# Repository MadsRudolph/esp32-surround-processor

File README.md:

# ESP32 surround processor

A four-speaker surround processor built around an ESP32. It takes the optical output of a TV, decodes Dolby Digital 5.1 in firmware, and drives two DACs: a front pair and a rear pair.

The receiver recovers the clocks from the optical signal and everything else follows them. The ESP32 is a slave on both of its I2S ports.

## What it does

- Dolby Digital 5.1 from the TV is decoded on the ESP32 and played on four speakers.
- Plain stereo goes to the fronts untouched, and the rears get a stereo matrix signal.
- DTS and Dolby Digital Plus are recognised and kept silent.
- A potentiometer sets the volume, and the board updates over Wi-Fi.

## The board

The board is 101.9 x 73.2 mm with copper on both faces, milled on a desktop CNC. The holes are not plated and there are no vias: the two faces meet only at 19 component leads soldered on both sides. The top face is a ground plane, and every clock, data and audio signal stays on the bottom. The layout is written as code, and a separate check proves the board is connected with bare holes, which KiCad's own rule check cannot do.

The pictures are renders made from the KiCad board file in Blender. The copper, the isolation channels, the legend and the part positions are the real design; the DAC and receiver modules are simplified stand-ins. The flat layer plots are in [docs/board.md](docs/board.md).

## Enclosure

A printed base with a laser-cut lid in 4 mm clear acrylic, held by M3 screws in heat-set inserts. The optical input, the coax input, four RCA outputs and the 9 V jack are on the rear panel, the volume knob on the front. The model uses caliper measurements of the real board and is collision-checked. The base is printed in PLA with a fuzzy-skin finish, and the box is assembled and tested (below). The files and the list of what is still assumed are in `enclosure/`.

## Measured

| | Result |
|---|---|
| Decode time | 5.3 ms average per 32 ms frame, with a film playing |
| Damaged frames | 0 in 48,044 |
| Channel separation | each channel on its own output, the others below -108 dBFS |
| Line outputs | 0.50 to 0.52 V rms at 1 kHz, -12 dBFS |
| Supply rails | 4.98 V and 3.21 V |

## Tested in the box

The finished box on its 9 V adapter, fed S/PDIF from an Analog Discovery 3 into the coax input (`tools/spdif_gen.py`), with the AD3's scope on the RCA outputs. The receiver locks in 2 to 3 s and the ESP32 reads exactly the −12.0 dBFS that is sent.

The rear matrix does what it should: half of left minus right on both rears, so a sound that is the same in both channels cancels by more than 47 dB and one that is in antiphase comes out at full level.

Every output carries its own channel at 0.46 to 0.49 V rms. That is 0.5 to 0.8 dB under the bench values, which were taken with a different signal source and different leads, so I read little into it. The right channel of each DAC is the lower one on both runs. The volume pot, mute (USER) and the mode button (BOOT) all work through the printed panel. The data and the plot script are `hardware/bench/box-test-2026-11-14.json` and `tools/plot_box_test.py`.

## What went wrong

- In the closed box on a 12 V adapter the LM317 that makes the 3.3 V got too hot, its output sagged, and the ESP32 reset from brown-out every second or so. On the 9 V adapter it is designed for, it runs without a reset. Feeding the LM317 from the 5 V rail would cut its heat by about 70 % and make a 12 V adapter safe.
- The vendor's I2S driver lost a 5 ms buffer now and then, because two interrupt handlers cleared each other's flags. A patched copy of the driver fixes it.
- The ESP32 drove its two data lines hard enough to disturb the clock lines beside them, and the DACs misread bits. The weakest drive setting is clean.
- The Dolby Digital decoder kept its FFT temporaries in doubles, and the ESP32 has no hardware for those. Single precision took the decode from 21 ms to about 5 ms per frame.

The full story is on the [project page](https://madsrudolph.dev/projects/esp32-surround-processor).

## Debug page

The board's debug page while a film plays. It shows the input format, levels and decoder health, and can play a chime or a sine sweep on one speaker at a time.

## More

- [docs/board.md](docs/board.md): file layout, rebuilding, fabrication rules, routing rules and the board concept
- [docs/firmware.md](docs/firmware.md): the firmware projects, build commands and the faults in detail
- [docs/bench.md](docs/bench.md): the bring-up page and the Analog Discovery 3
- [hardware/BUILD-NOTES.md](hardware/BUILD-NOTES.md): milling order, assembly order and module straps

## Status

The board is cut, soldered and working, and the firmware has been tested with a TV on four speakers. The enclosure is printed, assembled and tested with the AD3; the optical input with a TV in the box is next. The mute pin on the DAC modules does not mute, so mute is done in the audio data. Writing my own AC-3 decoder in place of liba52 is the next step.

## Licence

Copyright (C) 2026 Mads Rudolph. The firmware, the tools and the hardware design files
are free software under the **GNU General Public License, version 3 or (at your option)
any later version**; see `LICENSE`. They come with no warranty.

Two parts are other people's work and keep their own licences:

- `firmware/components/liba52/`: liba52 from a52dec 0.7.4, (C) Aaron Holtzman and Michel
  Lespinasse, GPL version 2 or later (`COPYING` in that folder). One file is changed, with a
  notice at its top.
- `firmware/components/esp_driver_i2s/`: the I2S driver from ESP-IDF v5.5, (C) Espressif
  Systems, Apache License 2.0 (`LICENSE` in that folder). One file is changed, with a notice
  at its top.

The firmware links both with ESP-IDF (Apache 2.0), which is why the whole is GPL version 3:
that is the GPL version compatible with the Apache licence.

"Dolby" and "Dolby Digital" are trademarks of Dolby Laboratories. This project is not made,
tested or endorsed by Dolby.

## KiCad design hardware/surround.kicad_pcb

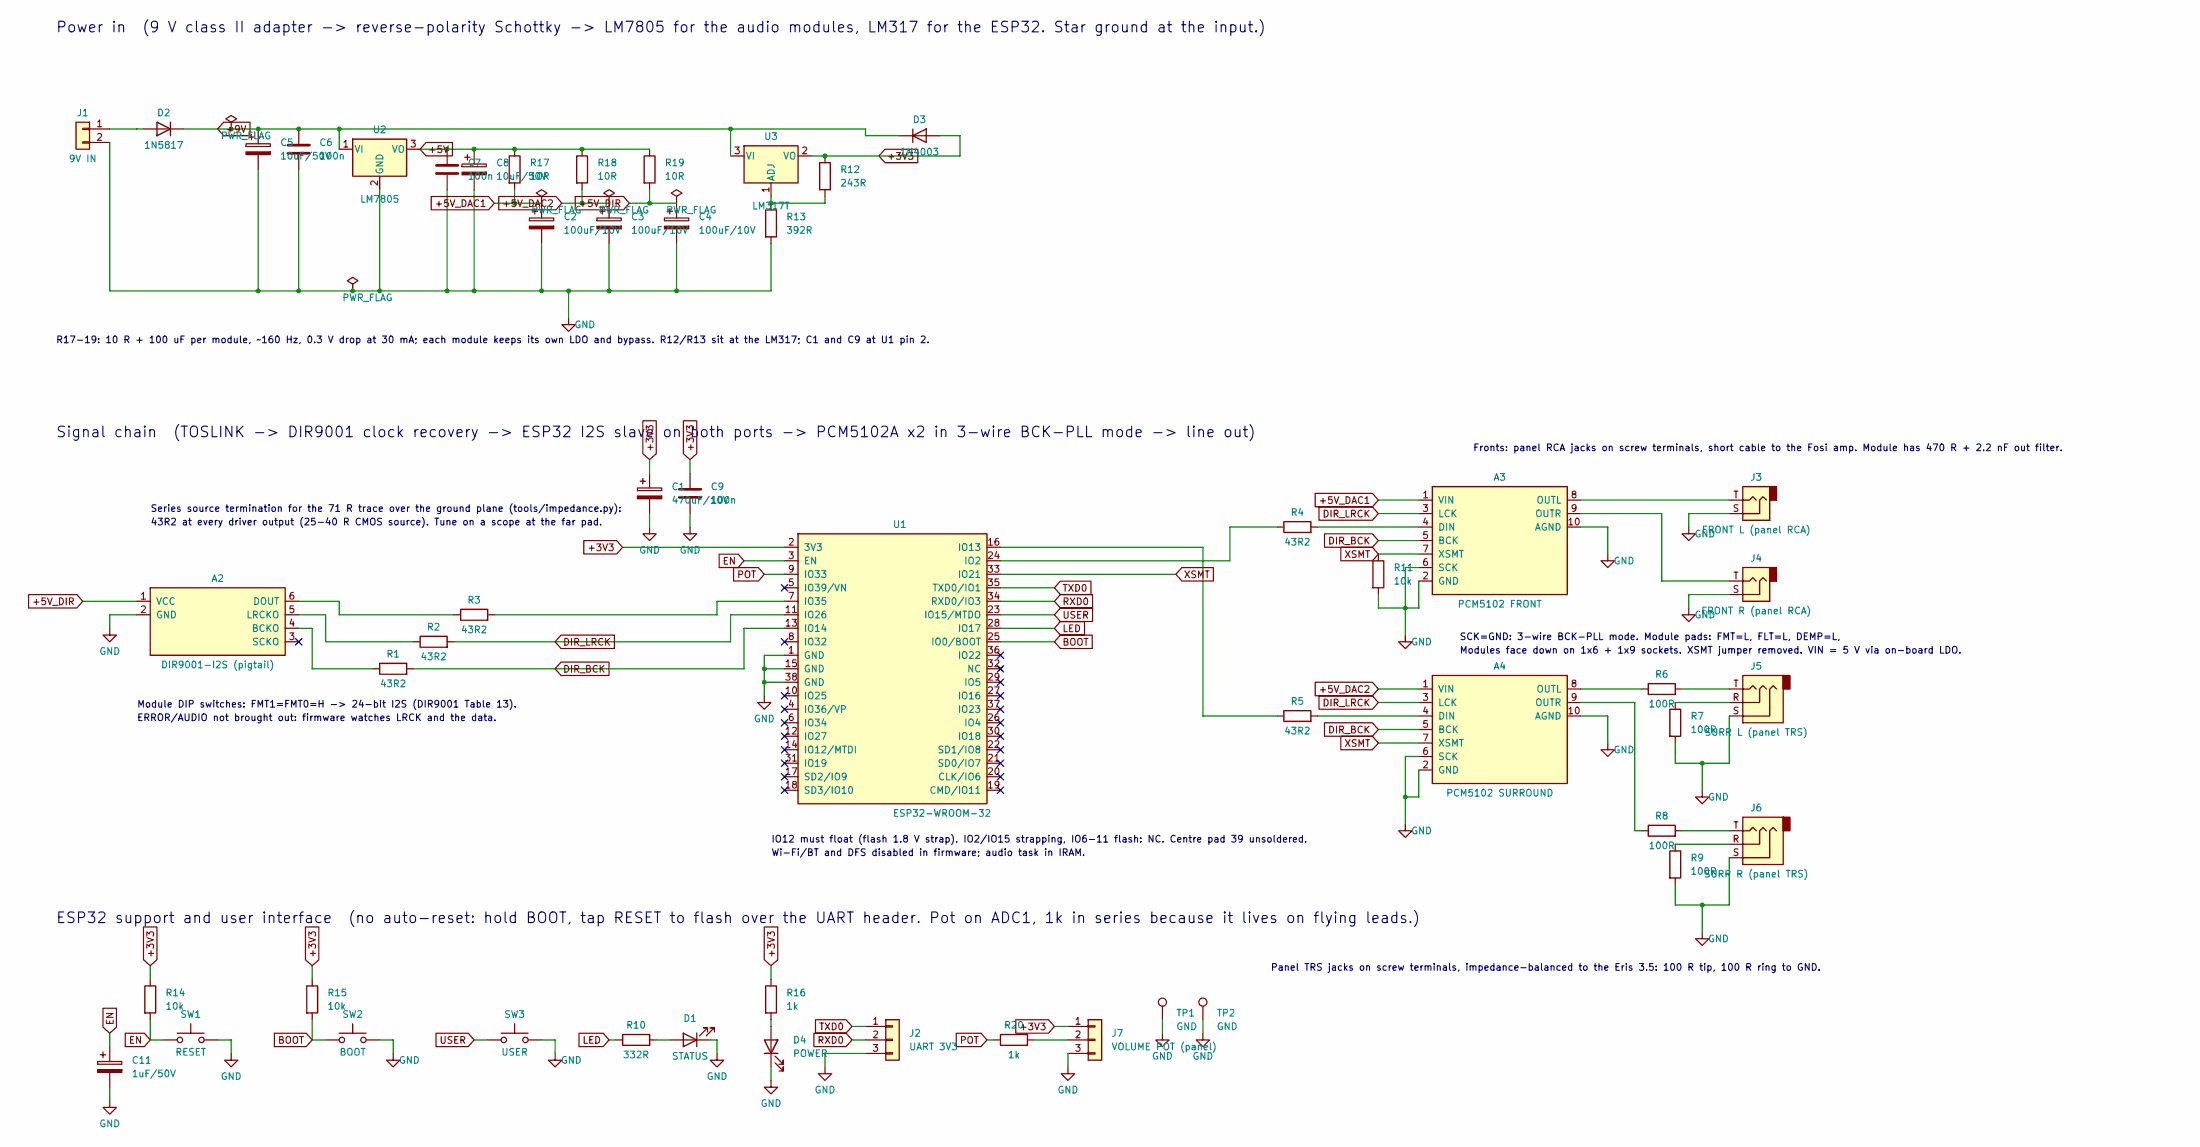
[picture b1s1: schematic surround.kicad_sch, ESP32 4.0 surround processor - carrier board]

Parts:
A2: DIR9001-I2S (pigtail); DIR9001_Pigtail_1x6
A3: PCM5102 FRONT; PCM5102_Module_FaceDown
A4: PCM5102 SURROUND; PCM5102_Module_FaceDown
C1: 470uF/10V; CP_Radial_D10.0mm_P5.00mm
C2, C3, C4: 100uF/10V; CP_Radial_D8.0mm_P5.00mm
C5, C8: 10uF/50V; CP_Radial_D5.0mm_P2.50mm
C6, C7, C9: 100n; C_Disc_D5.0mm_W2.5mm_P5.00mm
C11: 1uF/50V; CP_Radial_D5.0mm_P3.50mm_FormedLeads
D1: STATUS; LED_D3.0mm_P5.08mm_LaserPads
D2: 1N5817; D_DO-41_SOD81_P10.16mm_Horizontal
D3: 1N4003; D_DO-41_SOD81_P7.62mm_Horizontal
D4: POWER; LED_D3.0mm_P5.08mm_LaserPads
J1: 9V IN; TerminalBlock_2P_P5.08mm
J2: UART 3V3; PinHeader_1x03_P2.54mm_Vertical
J3: FRONT L (panel RCA); TerminalBlock_TS_P5.08mm
J4: FRONT R (panel RCA); TerminalBlock_TS_P5.08mm
J5: SURR L (panel TRS); TerminalBlock_TRS_P5.08mm
J6: SURR R (panel TRS); TerminalBlock_TRS_P5.08mm
J7: VOLUME POT (panel); PinHeader_1x03_P2.54mm_Vertical
R1, R2, R3, R4, R5: 43R2; R_Axial_DIN0207_L6.3mm_D2.5mm_P7.62mm_Horizontal
R6, R7, R8, R9: 100R; R_Axial_DIN0207_L6.3mm_D2.5mm_P7.62mm_Horizontal
R10: 332R; R_Axial_DIN0207_L6.3mm_D2.5mm_P7.62mm_Horizontal
R11, R14, R15: 10k; R_Axial_DIN0207_L6.3mm_D2.5mm_P7.62mm_Horizontal
R12: 243R; R_Axial_DIN0207_L6.3mm_D2.5mm_P7.62mm_Horizontal
R13: 392R; R_Axial_DIN0207_L6.3mm_D2.5mm_P7.62mm_Horizontal
R16, R20: 1k; R_Axial_DIN0207_L6.3mm_D2.5mm_P7.62mm_Horizontal
R17, R18, R19: 10R; R_Axial_DIN0207_L6.3mm_D2.5mm_P7.62mm_Horizontal
SW1: RESET; SW_PUSH_6mm
SW2: BOOT; SW_PUSH_6mm
SW3: USER; SW_PUSH_6mm
TP1, TP2: GND; TestPoint_THTPad_D2.0mm_Drill1.0mm
U1: ESP32-WROOM-32; ESP32-WROOM-32_NoVias
U2: LM7805; TO-220-3_Vertical_LaserPads
U3: LM317T; TO-220-3_Vertical_LaserPads

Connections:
+3V3: C1.1, C9.1, D3.2 (A), J7.1, R12.1, R14.1, R15.1, R16.1, U1.2 (3V3), U3.2 (VO)
+5V: C7.1, C8.1, R17.1, R18.1, R19.1, U2.3 (VO)
BOOT: R15.2, SW2.1, U1.25 (IO0/BOOT)
DIR_BCK: A3.5 (BCK), A4.5 (BCK), R1.2, U1.13 (IO14)
DIR_LRCK: A3.3 (LCK), A4.3 (LCK), R2.2, U1.11 (IO26)
EN: C11.1, R14.2, SW1.1, U1.3 (EN)
LED: R10.1, U1.28 (IO17)
unnamed: A2.4 (BCKO), R1.1
unnamed: A2.6 (DOUT), R3.1
unnamed: A2.5 (LRCKO), R2.1
unnamed: A3.4 (DIN), R4.2
unnamed: A3.8 (OUTL), J3.T
unnamed: A3.9 (OUTR), J4.T
unnamed: A4.4 (DIN), R5.2
unnamed: A4.8 (OUTL), R6.1
unnamed: A4.9 (OUTR), R8.1
unnamed: D1.2 (A), R10.2
unnamed: D2.2 (A), J1.1
unnamed: D4.2 (A), R16.2
unnamed: J5.R, R7.1
unnamed: J5.T, R6.2
unnamed: J6.R, R9.1
unnamed: J6.T, R8.2
unnamed: J7.2, R20.2
unnamed: R4.1, U1.24 (IO2)
unnamed: R5.1, U1.16 (IO13)
unnamed: R3.2, U1.7 (IO35)
unnamed: R12.2, R13.1, U3.1 (ADJ)
POT: R20.1, U1.9 (IO33)
RXD0: J2.2, U1.34 (RXD0/IO3)
TXD0: J2.1, U1.35 (TXD0/IO1)
USER: SW3.1, U1.23 (IO15/MTDO)
XSMT: A3.7 (XSMT), A4.7 (XSMT), R11.1, U1.33 (IO21)

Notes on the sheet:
Power in (9 V class II adapter -> reverse-polarity Schottky -> LM7805 for the audio modules, LM317 for the ESP32. Star ground at the input.)
R17-19: 10 R + 100 uF per module, ~160 Hz, 0.3 V drop at 30 mA; each module keeps its own LDO and bypass. R12/R13 sit at the LM317; C1 and C9 at U1 pin 2.
Signal chain (TOSLINK -> DIR9001 clock recovery -> ESP32 I2S slave on both ports -> PCM5102A x2 in 3-wire BCK-PLL mode -> line out)
Series source termination for the 71 R trace over the ground plane (tools/impedance.py):
43R2 at every driver output (25-40 R CMOS source). Tune on a scope at the far pad.
Module DIP switches: FMT1=FMT0=H -> 24-bit I2S (DIR9001 Table 13).
ERROR/AUDIO not brought out: firmware watches LRCK and the data.
IO12 must float (flash 1.8 V strap). IO2/IO15 strapping, IO6-11 flash: NC. Centre pad 39 unsoldered.
Wi-Fi/BT and DFS disabled in firmware; audio task in IRAM.
SCK=GND: 3-wire BCK-PLL mode. Module pads: FMT=L, FLT=L, DEMP=L,
Modules face down on 1x6 + 1x9 sockets. XSMT jumper removed. VIN = 5 V via on-board LDO.
Fronts: panel RCA jacks on screw terminals, short cable to the Fosi amp. Module has 470 R + 2.2 nF out filter.
Panel TRS jacks on screw terminals, impedance-balanced to the Eris 3.5: 100 R tip, 100 R ring to GND.
ESP32 support and user interface (no auto-reset: hold BOOT, tap RESET to flash over the UART header. Pot on ADC1, 1k in series because it lives on flying leads.)

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
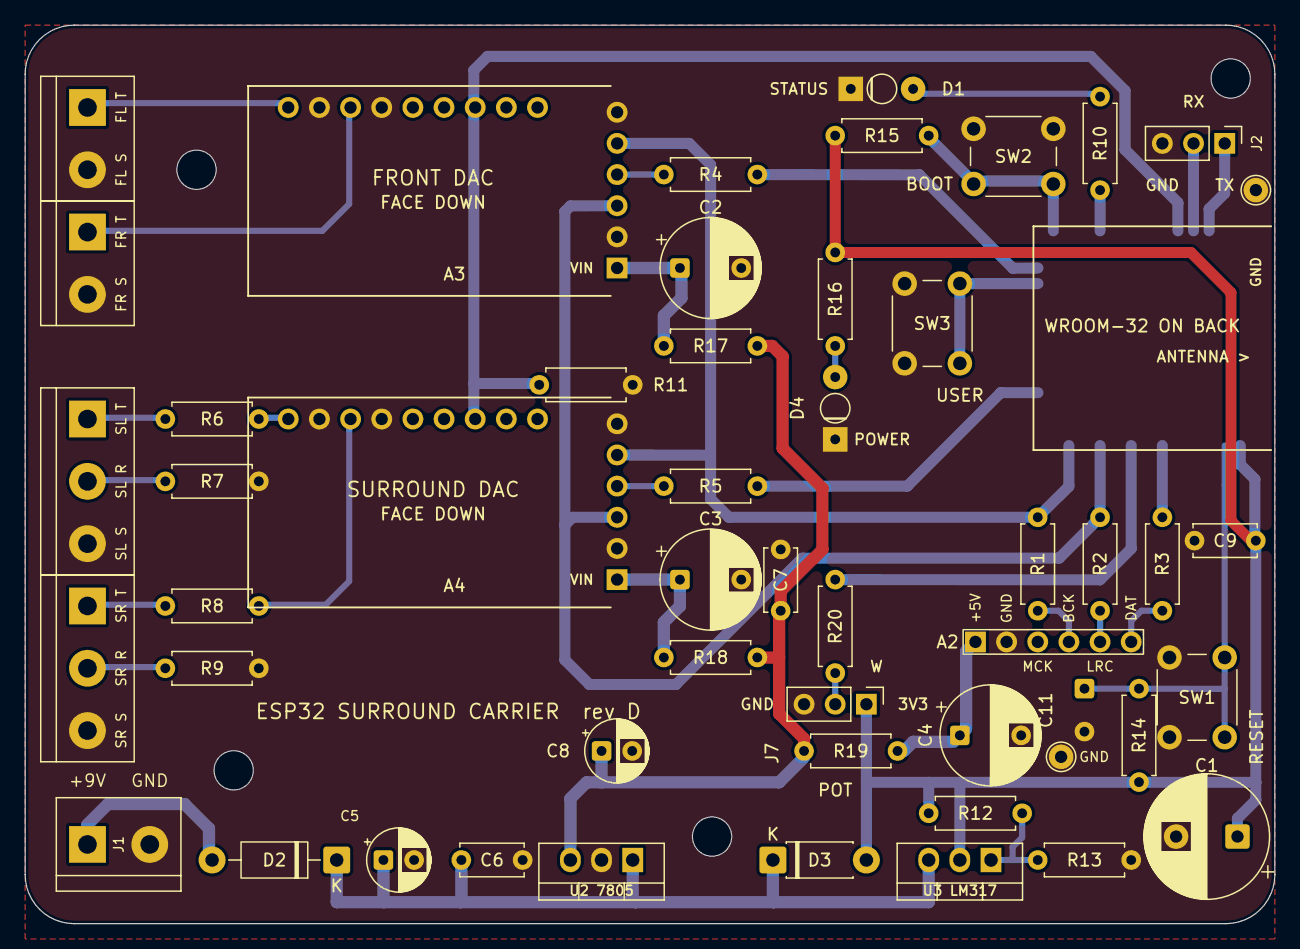
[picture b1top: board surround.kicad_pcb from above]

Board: 2 copper layers, 101.9 x 73.2 mm, 56 parts (1 on the bottom side), 38 nets.

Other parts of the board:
H1, H2, H3, H4: M3; MountingHole_3.2mm_M3

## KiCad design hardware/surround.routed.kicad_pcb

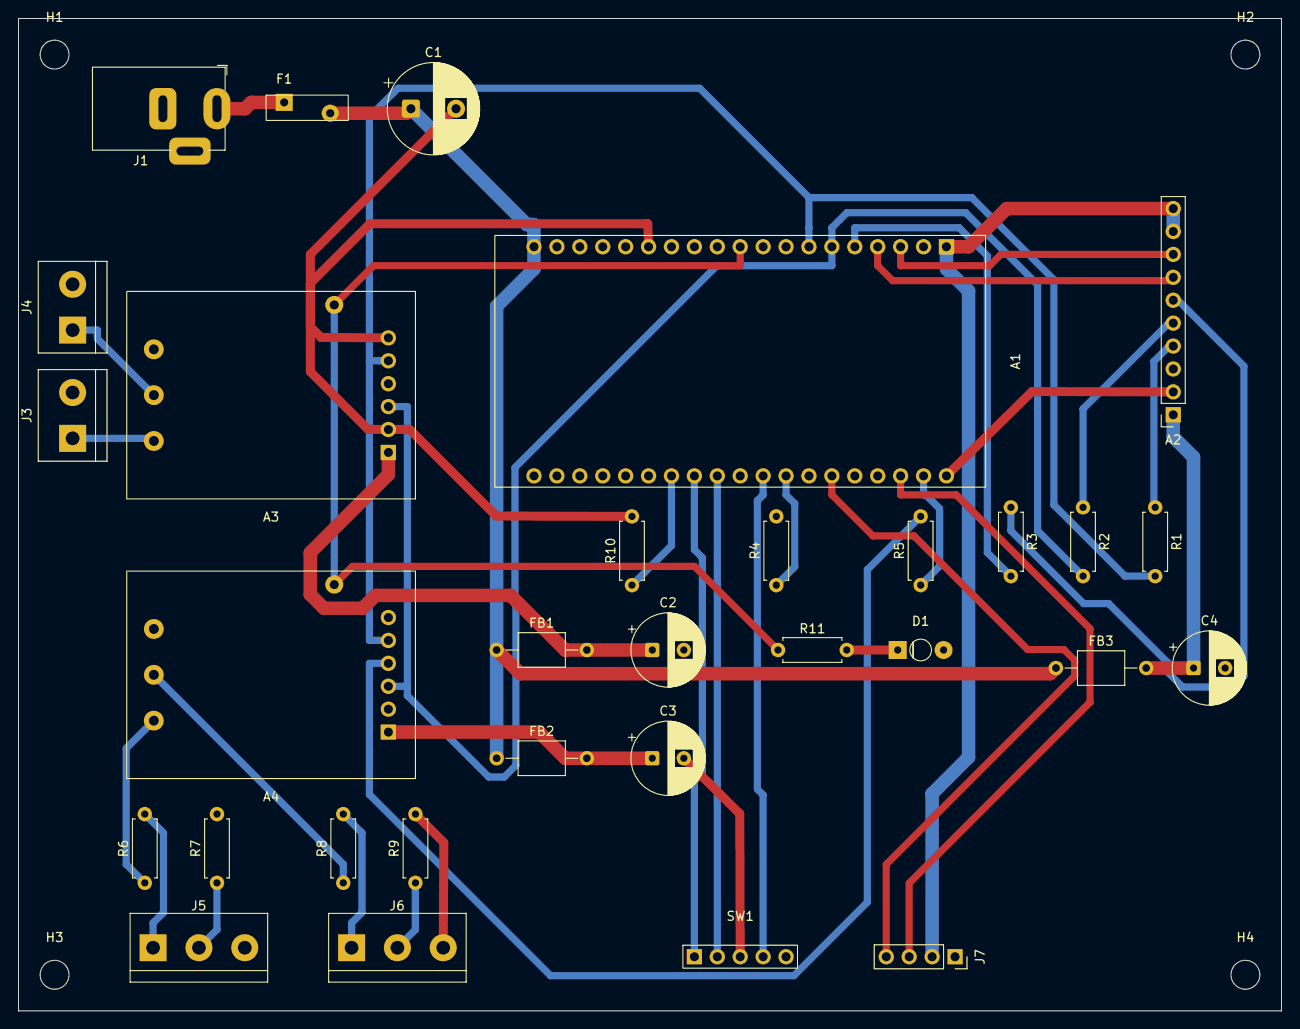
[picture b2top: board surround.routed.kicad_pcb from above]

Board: 2 copper layers, 140.0 x 110.0 mm, 35 parts (0 on the bottom side), 34 nets.

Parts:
A1: ESP32-DevKitC V4; ESP32-DevKitC-38_Sockets
A2: DIR9001 + TOSLINK; PinSocket_1x10_P2.54mm_Vertical
A3: GY-PCM5102 FRONT; GY-PCM5102_Carrier
A4: GY-PCM5102 SURROUND; GY-PCM5102_Carrier
C1: 470uF/10V; CP_Radial_D10.0mm_P5.00mm
C2, C3, C4: 100uF/10V; CP_Radial_D8.0mm_P3.50mm
D1: STATUS; LED_D3.0mm_P5.08mm_LaserPads
F1: MF-R110; Fuse_Bourns_MF-R110_P5.1mm
FB1, FB2, FB3: FB axial 600R; L_Axial_L5.0mm_D3.6mm_P10.00mm_Horizontal_Murata_BL01RN1A2A2
H1, H2, H3, H4: M3; MountingHole_3.2mm_M3
J1: PWR IN 5V; BarrelJack_Horizontal_MilledPads
J3: FRONT L (panel RCA); TerminalBlock_TS_P5.08mm
J4: FRONT R (panel RCA); TerminalBlock_TS_P5.08mm
J5: SURR L (panel TRS); TerminalBlock_TRS_P5.08mm
J6: SURR R (panel TRS); TerminalBlock_TRS_P5.08mm
J7: OLED SSD1306 I2C; PinSocket_1x04_P2.54mm_Vertical
R1, R2, R3, R4, R5: 56R; R_Axial_DIN0207_L6.3mm_D2.5mm_P7.62mm_Horizontal
R6, R7, R8, R9: 100R; R_Axial_DIN0207_L6.3mm_D2.5mm_P7.62mm_Horizontal
R10: 330R; R_Axial_DIN0207_L6.3mm_D2.5mm_P7.62mm_Horizontal
R11: 10k; R_Axial_DIN0207_L6.3mm_D2.5mm_P7.62mm_Horizontal
SW1: ENC (panel, 5 wires); PinHeader_1x05_Encoder

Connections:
+3V3: A1.1, A2.9, A2.10, J7.2
+5V: A1.19, C1.1, F1.2, FB1.1, FB2.1, FB3.1
+5V_DAC1: A3.1, C2.1, FB1.2
+5V_DAC2: A4.1, C3.1, FB2.2
+5V_DIR: A2.1, C4.1, FB3.2
DIR_BCK: A1.7, A3.5, A4.5, R1.2
DIR_LRCK: A1.6, A3.3, A4.3, R2.2
GND: A1.14, A1.20, A1.26, A2.2, A3.2, A3.6, A3.10, A4.2, A4.6, A4.10, C1.2, C2.2, C3.2, C4.2, D1.1, D1.2, J1.2, J3.S, J4.S, J5.S, J6.S, J7.1, R7.2, R9.2, R10.2, R11.2, SW1.C, SW1.S2
unnamed: A1.32, R10.1
unnamed: A1.31, SW1.A
unnamed: A1.30, SW1.B
unnamed: A1.28, SW1.S1
unnamed: A1.27, R4.1
unnamed: A1.21, R5.1
unnamed: A1.5, R3.2
unnamed: A1.3, A2.8
unnamed: A1.4, A2.7
unnamed: A2.4, R1.1
unnamed: A2.6, R3.1
unnamed: A2.5, R2.1
unnamed: A3.4, R4.2
unnamed: A3.8, J3.T
unnamed: A3.9, J4.T
unnamed: A4.4, R5.2
unnamed: A4.8, R6.1
unnamed: A4.9, R8.1
unnamed: F1.1, J1.1
unnamed: J5.R, R7.1
unnamed: J5.T, R6.2
unnamed: J6.R, R9.1
unnamed: J6.T, R8.2
SCL: A1.22, J7.3
SDA: A1.25, J7.4
XSMT: A1.10, A3.7, A4.7, R11.1

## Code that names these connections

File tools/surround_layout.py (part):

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    sh.seg(g, (G(121), g.y))
sh.seg((G(121), g1.y), (G(121), g38.y)); sh.gnd((G(121), g38.y))
ad = esp.pin("IO33")
sh.seg(ad, (G(121), ad.y)); sh.label((G(121), ad.y), "POT", rot=180, kind="global")
en = esp.pin("EN")
sh.seg(en, (G(118), en.y)); sh.label((G(118), en.y), "EN", rot=180, kind="global")
for nm in ("IO25", "IO36/VP", "IO34", "IO32", "IO27", "IO12/MTDI", "IO19", "SD2/IO9", "SD3/IO10",
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D2X, D2Y = G(230), G(117)
dac2 = sh.place("Surround:GY-PCM5102", "A4", at=(D2X, D2Y), value="PCM5102 SURROUND", footprint="Surround:PCM5102_Module_FaceDown")

din1, din2, xsmt_pin = esp.pin("IO2"), esp.pin("IO13"), esp.pin("IO21")
r4 = sh.place("Device:R", "R4", at=(G(200), dac1.pin("DIN").y), rot=90, value="43R2", footprint=RFP)
sh.seg(r4.pin(2), dac1.pin("DIN"))
sh.seg(din1, (G(190), din1.y)); sh.seg((G(190), din1.y), (G(190), r4.pin(1).y))
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sh.seg(r5.pin(2), d2din)
sh.seg(din2, (G(186), din2.y)); sh.seg((G(186), din2.y), (G(186), r5.pin(1).y))
sh.seg((G(186), r5.pin(1).y), r5.pin(1))
sh.seg(xsmt_pin, (G(182), xsmt_pin.y)); sh.label((G(182), xsmt_pin.y), "XSMT", kind="global")

LX = G(212)
for dac, pnet, rail_y in ((dac1, "+5V_DAC1", G(99)), (dac2, "+5V_DAC2", G(127))):
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    sh.seg(sck, (G(216), sck.y))
    pts = [(G(216), sck.y), gnd]
    if dac is dac1:                              # XSMT pull-down: muted through boot
        r11 = sh.place("Device:R", "R11", at=(LX, dac.pin("XSMT").y + G(3)), value="10k", footprint=RFP)
        pts.append(r11.pin(2))
    gnd_rail(sh, pts, rail_y, x_sym=G(216))
sh.note((G(224), G(104)), "SCK=GND: 3-wire BCK-PLL mode. Module pads: FMT=L, FLT=L, DEMP=L,", size=1.27)
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    """A short wire from a right-hand ESP32 pin to a global label."""
    sh.seg(pin, (x, pin.y)); sh.label((x, pin.y), net, kind="global")
stub(esp.pin("IO0/BOOT"), G(164), "BOOT")
stub(esp.pin("IO15/MTDO"), G(164), "USER")
stub(esp.pin("IO17"), G(164), "LED")
stub(esp.pin("TXD0/IO1"), G(164), "TXD0")
stub(esp.pin("RXD0/IO3"), G(164), "RXD0")
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pullup("R15", boot_node[0], boot_node, "BOOT")
# user button: internal pull-up in firmware
user_node = button("SW3", G(84), "USER", "USER")
sh.label(user_node, "USER", rot=180, kind="global")
# status LED
r10 = sh.place("Device:R", "R10", at=(G(102), SUP_Y + G(3)), rot=90, value="332R", footprint=RFP)
sh.seg(r10.pin(1), (G(98), r10.pin(1).y)); sh.label((G(98), r10.pin(1).y), "LED", rot=180, kind="global")
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sh.seg(j2.pin(3), (G(130), j2.pin(3).y)); sh.gnd((G(130), j2.pin(3).y))
# volume pot, panel mounted on three wires
r20 = sh.place("Device:R", "R20", at=(G(158), SUP_Y + G(3)), rot=90, value="1k", footprint=RFP)
sh.seg(r20.pin(1), (G(154), r20.pin(1).y)); sh.label((G(154), r20.pin(1).y), "POT", rot=180, kind="global")
j7 = sh.place("Connector_Generic:Conn_01x03", "J7", at=(G(170), SUP_Y + G(3)), value="VOLUME POT (panel)", footprint="Connector_PinHeader_2.54mm:PinHeader_1x03_P2.54mm_Vertical")
sh.seg(j7.pin(2), r20.pin(2))
sh.seg(j7.pin(1), (G(164), j7.pin(1).y)); sh.label((G(164), j7.pin(1).y), "+3V3", rot=180, kind="global")
sh.seg(j7.pin(3), (G(166), j7.pin(3).y)); sh.gnd((G(166), j7.pin(3).y))
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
